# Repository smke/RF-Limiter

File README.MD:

# RF Limiter

Simple RF Power Limiter based on design from EEVBlog. Design made in KiCAD as an exercise to learn how to use it.

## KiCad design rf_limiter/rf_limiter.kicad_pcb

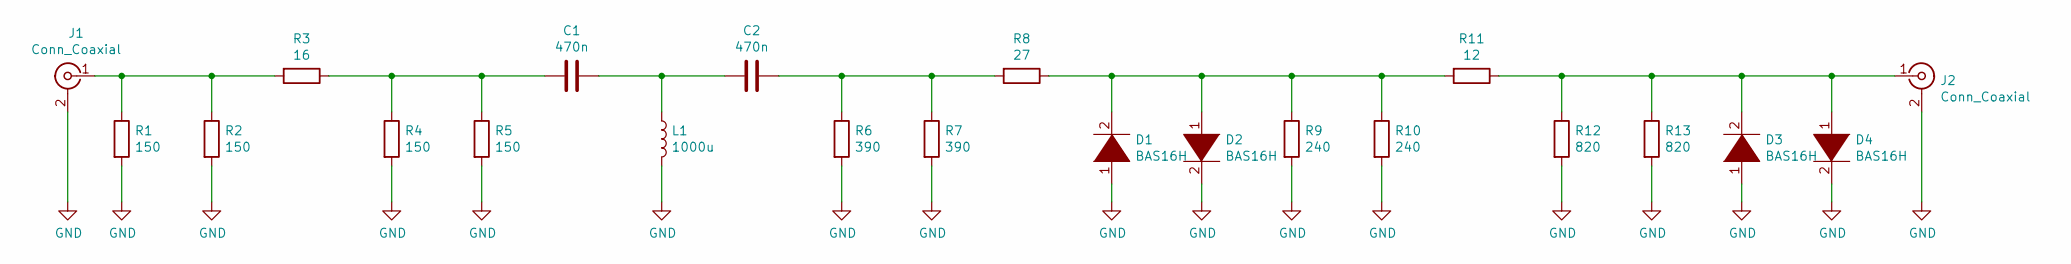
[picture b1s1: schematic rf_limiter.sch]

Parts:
C1, C2: 470n; C_0805
D1, D2, D3, D4: BAS16H; D_SOD-123
J1, J2: Conn_Coaxial; SMA_THT_Jack_Straight
L1: 1000u; L_7.3x7.3_H3.5; Part Number SLF7032T-102MR13-2PF
R1, R2, R4, R5: 150; R_0805
R3: 16; R_1210
R6, R7: 390; R_0805
R8: 27; R_1210
R9, R10: 240; R_0805
R11: 12; R_1210
R12, R13: 820; R_0805

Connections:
GND: D1.1 (K), D2.2 (A), D3.1 (K), D4.2 (A), J1.2 (Ext), J2.2 (Ext), L1.2, R1.2, R2.2, R4.2, R5.2, R6.2, R7.2, R9.2, R10.2, R12.2, R13.2
unnamed: C1.1, C2.2, L1.1
unnamed: C1.2, R3.1, R4.1, R5.1
unnamed: C2.1, R6.1, R7.1, R8.2
unnamed: D1.2 (A), D2.1 (K), R8.1, R9.1, R10.1, R11.2
unnamed: D3.2 (A), D4.1 (K), J2.1 (In), R11.1, R12.1, R13.1
unnamed: J1.1 (In), R1.1, R2.1, R3.2

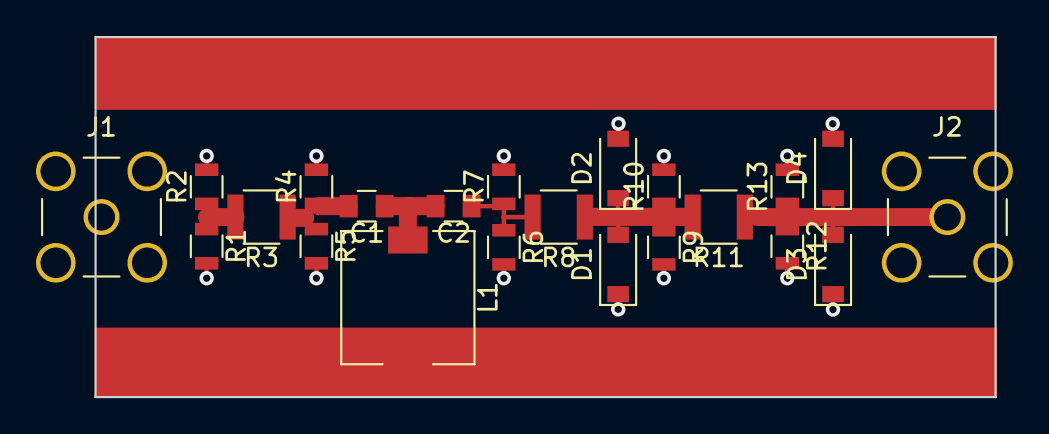
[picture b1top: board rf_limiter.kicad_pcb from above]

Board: 2 copper layers, 50.0 x 20.0 mm, 22 parts (0 on the bottom side), 7 nets.

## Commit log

2019-06-03 Committed inital information
2019-06-03 Committed inital PCB layout and schematic. Some major learning needed to get Kicad working smoothly.
2019-06-03 Committed some layout changes. Still need to work out RF stuff. Layout tool is a bit strange when it comes to snapping. Target to fit within 50x50mm PCB
2019-06-03 Added README.MD
